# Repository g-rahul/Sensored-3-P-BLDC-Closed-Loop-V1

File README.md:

# Sensored-3-P-BLDC-Closed-Loop-V1
This Firmware was developed as an extension of  Ti's Sensored close-loop BLDC motor control using MSP430. 
Ti's application firmware for MSP430 has been modified for STM32F103 Series MCU's.

This firmware was developed by
* Rahul (rep owner)
* https://github.com/g-rahul
* RVCE
* July 2020

Target-STM32F103C8T6
IDE- MDK Keil uVision 5

The author would like to credit the orignal code developer on whose idea this code is based upon
 * Bhargavi Nisarga 
 * Texas Instruments Inc. 
 * Dec 2010
 * Built with IAR Version:4.2 and CCS v4.2
 
 More information on Ti's MSP430 application can be found at https://www.ti.com/lit/an/slaa503/slaa503.pdf?ts=1596031062777&ref_url=https%253A%252F%252Fwww.google.com%252F & 
 http://www.ti.com/lit/zip/slaa503.

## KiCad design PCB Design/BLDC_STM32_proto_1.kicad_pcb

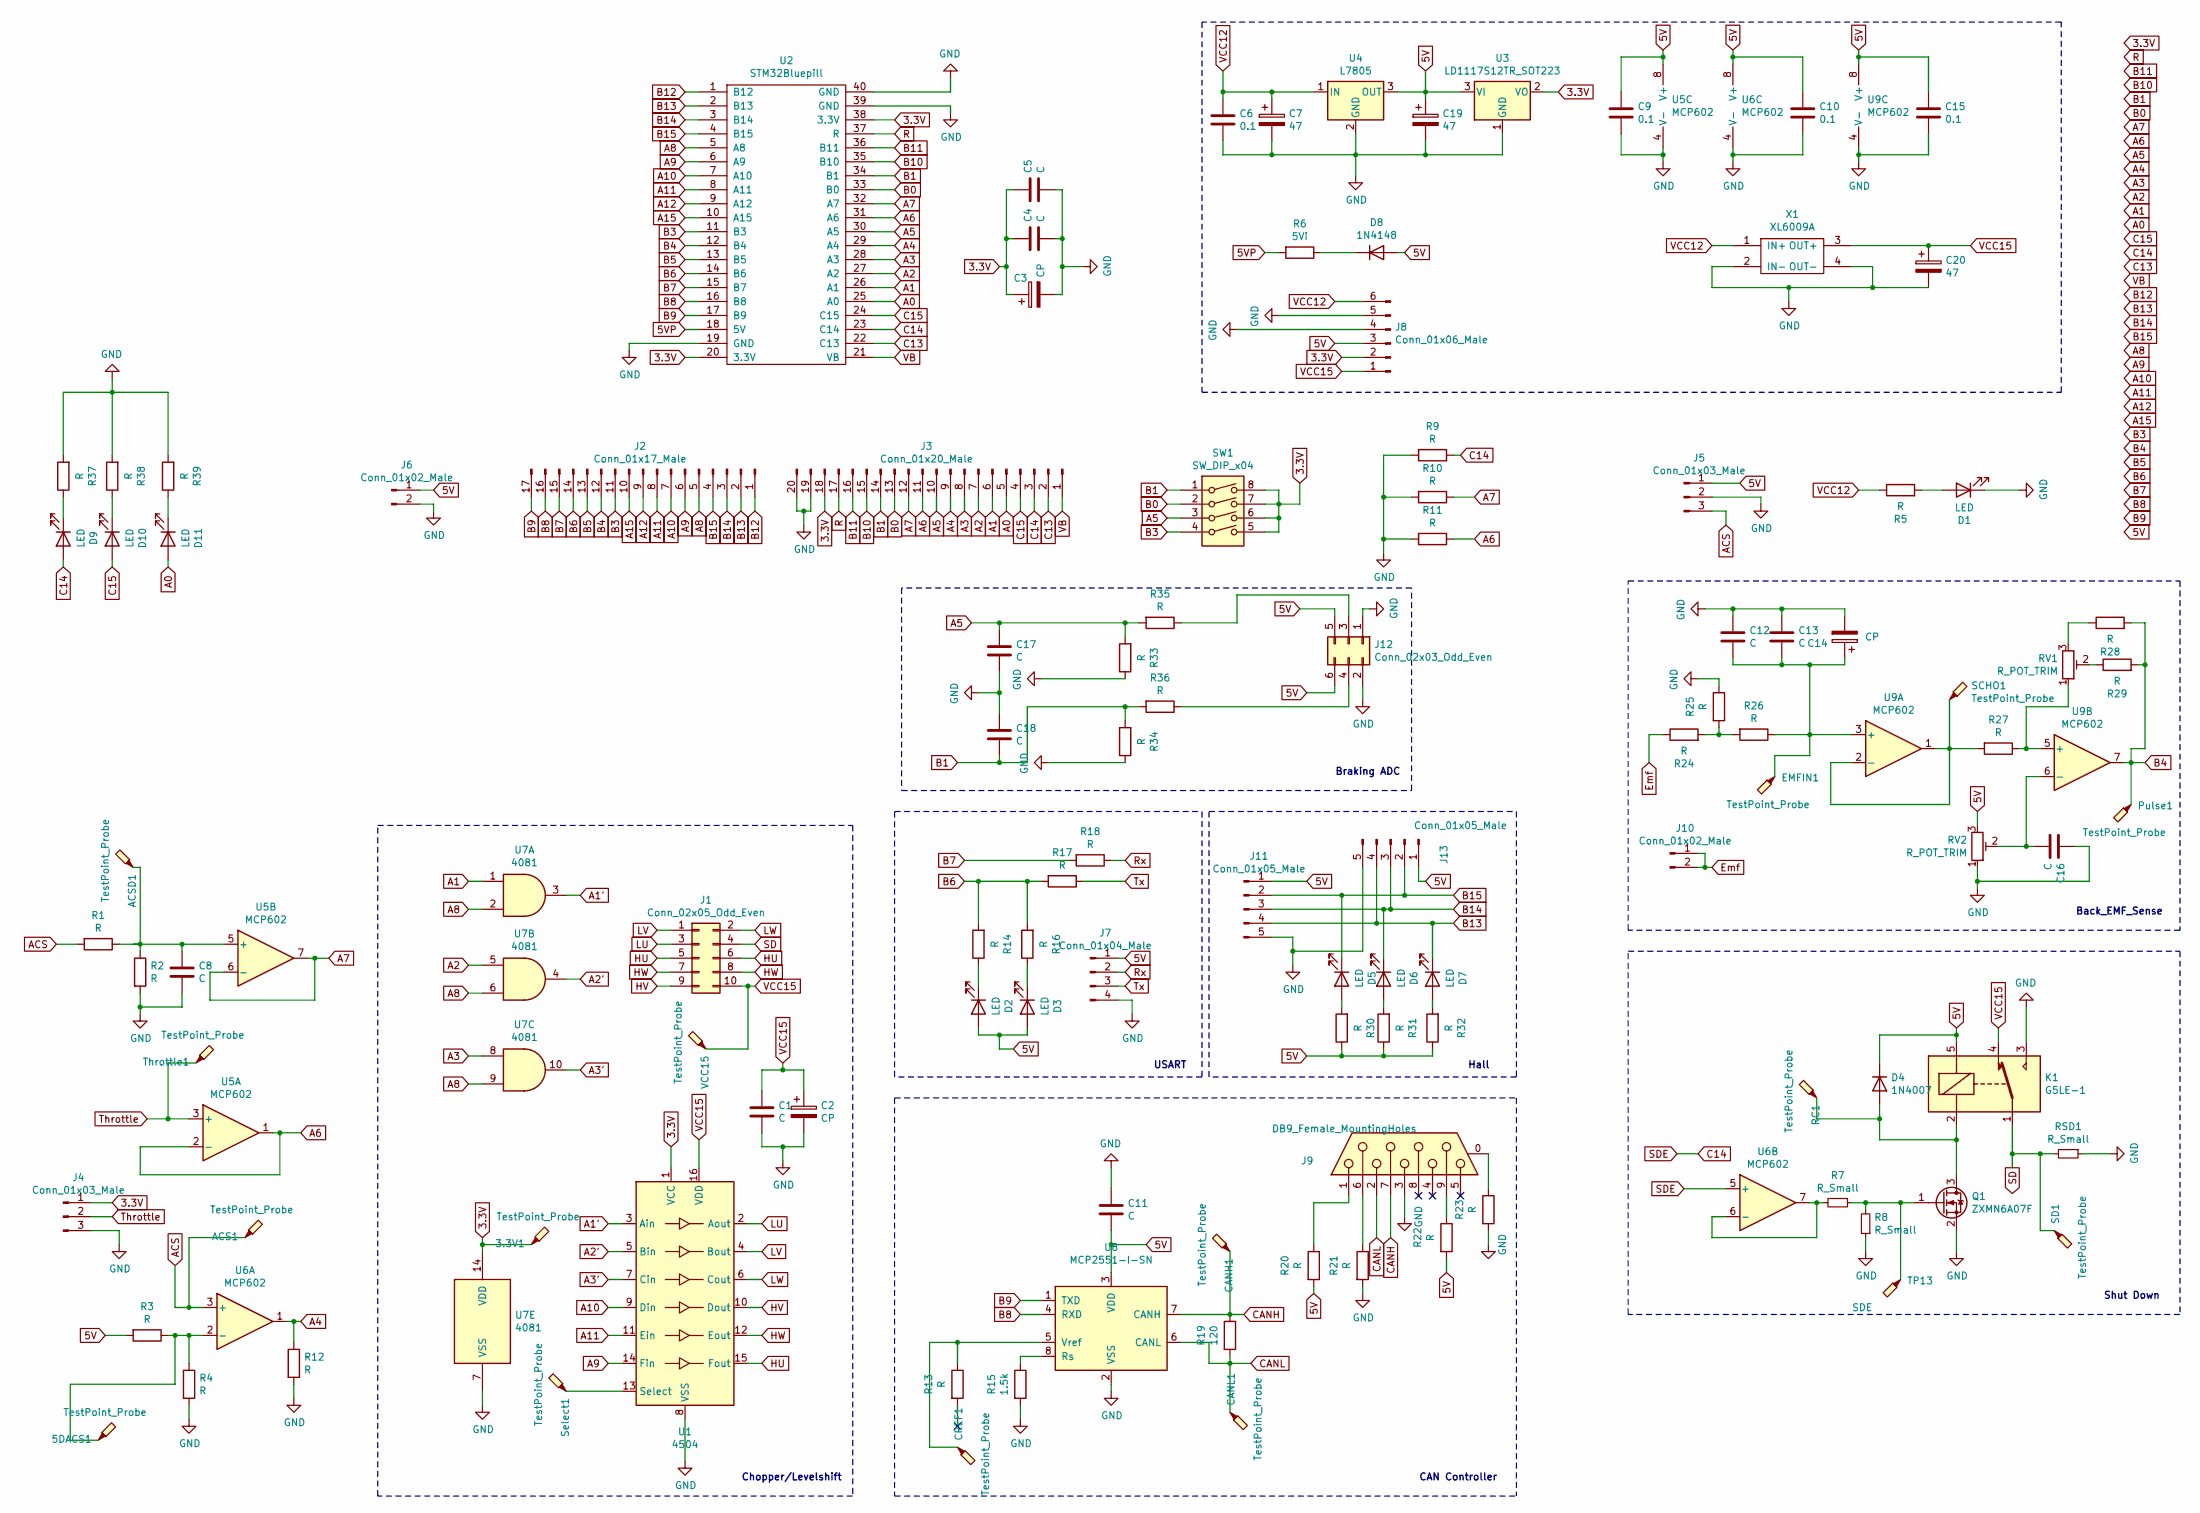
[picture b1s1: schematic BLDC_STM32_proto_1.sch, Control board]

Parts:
3.3V1, 5DACS1: TestPoint_Probe; TestPoint_Loop_D1.80mm_Drill1.0mm_Beaded
ACS1: TestPoint_Probe; TestPoint_Loop_D1.80mm_Drill1.0mm_Beaded
ACSD1: TestPoint_Probe; TestPoint_Loop_D1.80mm_Drill1.0mm_Beaded
C1, C4, C5, C8, C11, C12, C13, C16, C17, C18: C; C_1206_3216Metric_Pad1.42x1.75mm_HandSolder
C2, C3, C14: CP; CP_Radial_D8.0mm_P3.80mm
C6, C9, C10, C15: 0.1; C_1206_3216Metric_Pad1.42x1.75mm_HandSolder
C7, C19, C20: 47; CP_Radial_D8.0mm_P3.80mm
CANH1: TestPoint_Probe; TestPoint_Loop_D1.80mm_Drill1.0mm_Beaded
CANL1: TestPoint_Probe; TestPoint_Loop_D1.80mm_Drill1.0mm_Beaded
CREF1: TestPoint_Probe; TestPoint_Loop_D1.80mm_Drill1.0mm_Beaded
D1, D2, D3, D9, D10, D11: LED; LED_1206_3216Metric
D4: 1N4007; D_DO-41_SOD81_P10.16mm_Horizontal
D5, D6, D7: LED; LED_0805_2012Metric
D8: 1N4148; D_DO-35_SOD27_P7.62mm_Horizontal
EMFIN1: TestPoint_Probe; TestPoint_Loop_D1.80mm_Drill1.0mm_Beaded
J1: Conn_02x05_Odd_Even; IDC-Header_2x05_P2.54mm_Horizontal
J2: Conn_01x17_Male; PinSocket_1x17_P2.54mm_Vertical
J3: Conn_01x20_Male; PinSocket_1x20_P2.54mm_Vertical
J4, J5: Conn_01x03_Male; PinHeader_1x03_P2.54mm_Vertical
J6: Conn_01x02_Male; PinHeader_1x02_P2.54mm_Vertical
J7: Conn_01x04_Male; PinHeader_1x04_P2.54mm_Vertical
J8: Conn_01x06_Male; JST_VH_B6P-VH-B_1x06_P3.96mm_Vertical
J9: DB9_Female_MountingHoles; DSUB-9_Female_Horizontal_P2.77x2.84mm_EdgePinOffset9.90mm_H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
J10: Conn_01x02_Male; JST_VH_B2P-VH-B_1x02_P3.96mm_Vertical
J11: Conn_01x05_Male; JST_EH_B5B-EH-A_1x05_P2.50mm_Vertical
J12: Conn_02x03_Odd_Even; PinHeader_2x03_P2.54mm_Vertical_SMD
J13: Conn_01x05_Male; PinHeader_1x05_P2.54mm_Vertical
K1: G5LE-1; Relay_SPDT_Omron-G5LE-1
Pulse1: TestPoint_Probe; TestPoint_Loop_D1.80mm_Drill1.0mm_Beaded
Q1: ZXMN6A07F; SOT-23
R1, R2: R; R_Axial_DIN0207_L6.3mm_D2.5mm_P5.08mm_Vertical
R3, R4, R5, R9, R10, R11, R12, R13, R24, R25, R26, R27, R28, R29, R33, R34, R35, R36: R; R_1206_3216Metric_Pad1.42x1.75mm_HandSolder
R6: 5Vi; R_1206_3216Metric_Pad1.42x1.75mm_HandSolder
R7, R8: R_Small; R_1206_3216Metric_Pad1.42x1.75mm_HandSolder
R14, R16, R17, R18, R20, R21, R22, R23, R30, R31, R32, R37, R38, R39: R; R_0805_2012Metric
R15: 1.5k; R_1206_3216Metric_Pad1.42x1.75mm_HandSolder
R19: 120; R_1206_3216Metric_Pad1.42x1.75mm_HandSolder
RC1: TestPoint_Probe; TestPoint_Loop_D1.80mm_Drill1.0mm_Beaded
RSD1: R_Small; R_1206_3216Metric_Pad1.42x1.75mm_HandSolder
RV1, RV2: R_POT_TRIM; Potentiometer_Bourns_3296W_Vertical
SCHO1: TestPoint_Probe; TestPoint_Loop_D1.80mm_Drill1.0mm_Beaded
SD1: TestPoint_Probe; TestPoint_Loop_D1.80mm_Drill1.0mm_Beaded
SW1: SW_DIP_x04; DIP-8_W7.62mm_LongPads
Select1: TestPoint_Probe; TestPoint_Loop_D1.80mm_Drill1.0mm_Beaded
TP13: SDE; TestPoint_Loop_D1.80mm_Drill1.0mm_Beaded
Throttle1: TestPoint_Probe; TestPoint_Loop_D1.80mm_Drill1.0mm_Beaded
U1: 4504; DIP-16_W7.62mm
U2: STM32Bluepill
U3: LD1117S12TR_SOT223; SOT-223-3_TabPin2
U4: L7805; TO-263-2
U5, U6, U9: MCP602; SOIC-8_3.9x4.9mm_P1.27mm
U7: 4081; DIP-14_W7.62mm
U8: MCP2551-I-SN; SOIC-8_3.9x4.9mm_P1.27mm
VCC15: TestPoint_Probe; TestPoint_Loop_D1.80mm_Drill1.0mm_Beaded
X1: XL6009A; XL6009

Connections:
3.3V: 3.3V1.1, C3.1, C4.1, C5.1, J3.18, J4.1, J8.2, SW1.5, SW1.6, SW1.7, SW1.8, U1.1 (VCC), U2.20 (3.3V), U2.38 (3.3V), U3.2 (VO), U7.14 (VDD)
5V: C9.1, C10.1, C11.2, C15.1, C19.1, D2.2 (A), D3.2 (A), D4.1 (K), D8.2 (A), J5.1, J6.1, J7.1, J8.3, J11.1, J12.5, J12.6, J13.1, K1.5, R3.2, R20.2, R22.2, R30.1, R31.1, R32.1, RV2.3, U3.3 (VI), U4.3 (OUT), U5.8 (V+), U6.8 (V+), U8.3 (VDD), U9.8 (V+)
5VP: R6.2, U2.18 (5V)
A0: D11.2 (A), J3.5, U2.25 (A0)
A1: J3.6, U2.26 (A1), U7.1
A1': U1.3 (Ain), U7.3
A2: J3.7, U2.27 (A2), U7.5
A2': U1.5 (Bin), U7.4
A3: J3.8, U2.28 (A3), U7.8
A3': U1.7 (Cin), U7.10
A4: J3.9, R12.1, U2.29 (A4), U6.1
A5: C17.1, J3.10, R33.2, R35.2, SW1.3, U2.30 (A5)
A6: J3.11, R11.1, U2.31 (A6), U5.1, U5.2 (-)
A7: J3.12, R10.1, U2.32 (A7), U5.6 (-), U5.7
A8: J2.5, U2.5 (A8), U7.2, U7.6, U7.9
A9: J2.6, U1.14 (Fin), U2.6 (A9)
A10: J2.7, U1.9 (Din), U2.7 (A10)
A11: J2.8, U1.11 (Ein), U2.8 (A11)
A12: J2.9, U2.9 (A12)
A15: J2.10, U2.10 (A15)
ACS: ACS1.1, J5.3, R1.2, U6.3 (+)
B0: J3.13, SW1.2, U2.33 (B0)
B1: C18.2, J3.14, R34.2, R36.2, SW1.1, U2.34 (B1)
B3: J2.11, SW1.4, U2.11 (B3)
B4: J2.12, Pulse1.1, R28.2, R29.2, U2.12 (B4), U9.7
B5: J2.13, U2.13 (B5)
B6: J2.14, R14.2, R16.2, R17.2, U2.14 (B6)
B7: J2.15, R18.2, U2.15 (B7)
B8: J2.16, U2.16 (B8), U8.4 (RXD)
B9: J2.17, U2.17 (B9), U8.1 (TXD)
B10: J3.15, U2.35 (B10)
B11: J3.16, U2.36 (B11)
B12: J2.1, U2.1 (B12)
B13: D7.1 (K), J2.2, J11.4, J13.4, U2.2 (B13)
B14: D6.1 (K), J2.3, J11.3, J13.3, U2.3 (B14)
B15: D5.1 (K), J2.4, J11.2, J13.2, U2.4 (B15)
C13: J3.2, U2.22 (C13)
C14: D9.2 (A), J3.3, R9.1, U2.23 (C14), U6.5 (+)
C15: D10.2 (A), J3.4, U2.24 (C15)
CANH: CANH1.1, J9.7, R19.1, U8.7 (CANH)
CANL: CANL1.1, J9.2, R19.2, U8.6 (CANL)
Emf: J10.1, J10.2, R24.1
GND: C1.2, C2.2, C3.2, C4.2, C5.2, C6.2, C7.2, C8.2, C9.2, C10.2, C11.1, C12.1, C13.1, C14.2, C15.2, C16.1, C17.2, C18.1, C19.2, C20.2, D1.1 (K), J3.19, J3.20, J4.3, J5.2, J6.2, J7.4, J8.4, J8.5, J9.3, J11.5, J12.1, J12.2, J13.5, K1.3, Q1.2 (S), R2.2, R4.2, R8.1, R9.2, R10.2, R11.2, R12.2, R15.2, R21.2, R23.2, R25.1, R33.1, R34.1, R37.2, R38.2, R39.2, RSD1.1, RV2.1, U1.8 (VSS), U2.19 (GND), U2.39 (GND), U2.40 (GND), U3.1 (GND), U4.2 (GND), U5.4 (V-), U6.4 (V-), U7.7 (VSS), U8.2 (VSS), U9.4 (V-), X1.2 (IN-), X1.4 (OUT-); also elsewhere on the board
HU: J1.5, J1.6, U1.15 (Fout)
HV: J1.9, U1.10 (Dout)
HW: J1.7, J1.8, U1.12 (Eout)
LU: J1.3, U1.2 (Aout)
LV: J1.1, U1.4 (Bout)
LW: J1.2, U1.6 (Cout)
unnamed: 5DACS1.1, R3.1, R4.1, U6.2 (-)
unnamed: ACSD1.1, C8.1, R1.1, R2.1, U5.5 (+)
unnamed: C12.2, C13.2, C14.1, EMFIN1.1, R26.1, U9.3 (+)
unnamed: C16.2, RV2.2, U9.6 (-)
unnamed: CREF1.1, R13.1, U8.5 (Vref)
unnamed: D1.2 (A), R5.2
unnamed: D2.1 (K), R14.1
unnamed: D3.1 (K), R16.1
unnamed: D4.2 (A), K1.2, Q1.3 (D), RC1.1
unnamed: D5.2 (A), R30.2
unnamed: D6.2 (A), R31.2
unnamed: D7.2 (A), R32.2
unnamed: D8.1 (K), R6.1
unnamed: D9.1 (K), R37.1
unnamed: D10.1 (K), R38.1
unnamed: D11.1 (K), R39.1
unnamed 65: J9.0 (PAD), R23.1; also elsewhere on the board
unnamed: J9.1, R20.1
unnamed: J9.6, R21.1
unnamed: J9.9, R22.1
unnamed: J12.3, R35.1
unnamed: J12.4, R36.1
unnamed: Q1.1 (G), R7.1, R8.2, TP13.1
unnamed: R7.2, U6.6 (-), U6.7
unnamed: R15.1, U8.8 (Rs)
unnamed: R24.2, R25.2, R26.2
unnamed: R27.1, RV1.1, U9.5 (+)
unnamed: R27.2, SCHO1.1, U9.1, U9.2 (-)
unnamed: R28.1, RV1.3
unnamed: R29.1, RV1.2
unnamed: Select1.1, U1.13 (Select)
R: J3.17, U2.37 (R)
Rx: J7.2, R18.1
SD: J1.4, K1.1, RSD1.2, SD1.1
Throttle: J4.2, Throttle1.1, U5.3 (+)
Tx: J7.3, R17.1
VB: J3.1, U2.21 (VB)
VCC12: C6.1, C7.1, J8.6, R5.1, U4.1 (IN), X1.1 (IN+)
VCC15: C1.1, C2.1, C20.1, J1.10, J8.1, K1.4, U1.16 (VDD), VCC15.1, X1.3 (OUT+)

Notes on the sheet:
CAN Controller
Shut Down
USART
Back_EMF_Sense
Chopper/Levelshift
Hall
Braking ADC

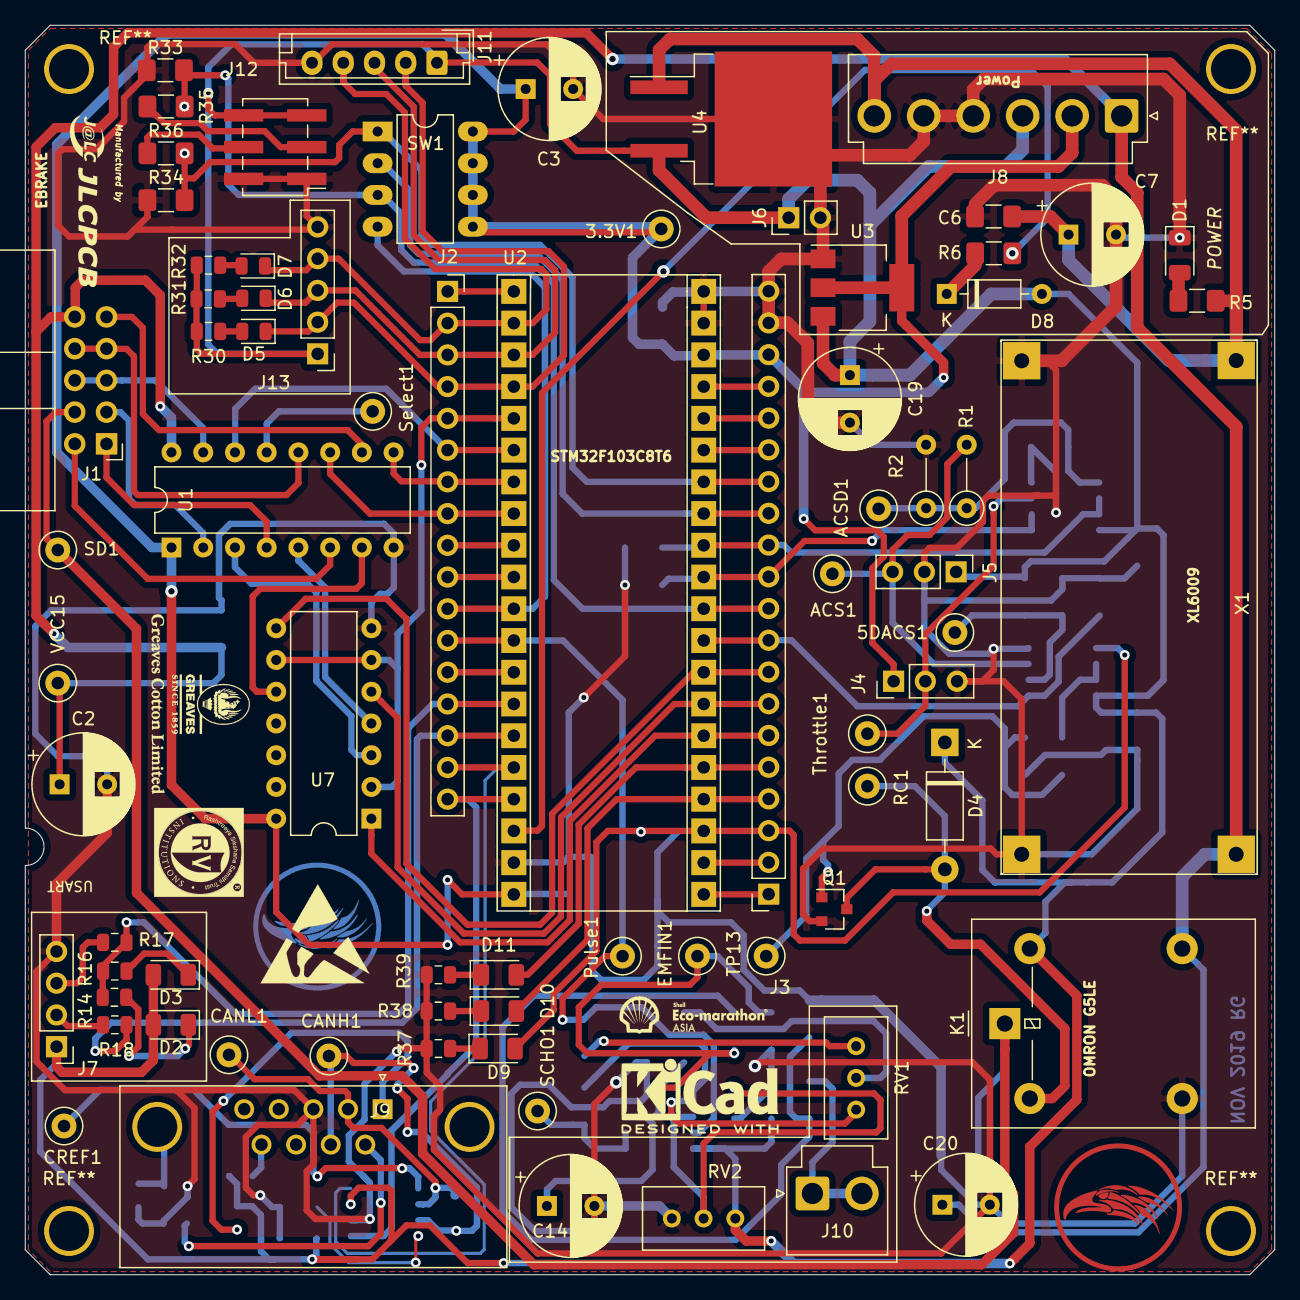
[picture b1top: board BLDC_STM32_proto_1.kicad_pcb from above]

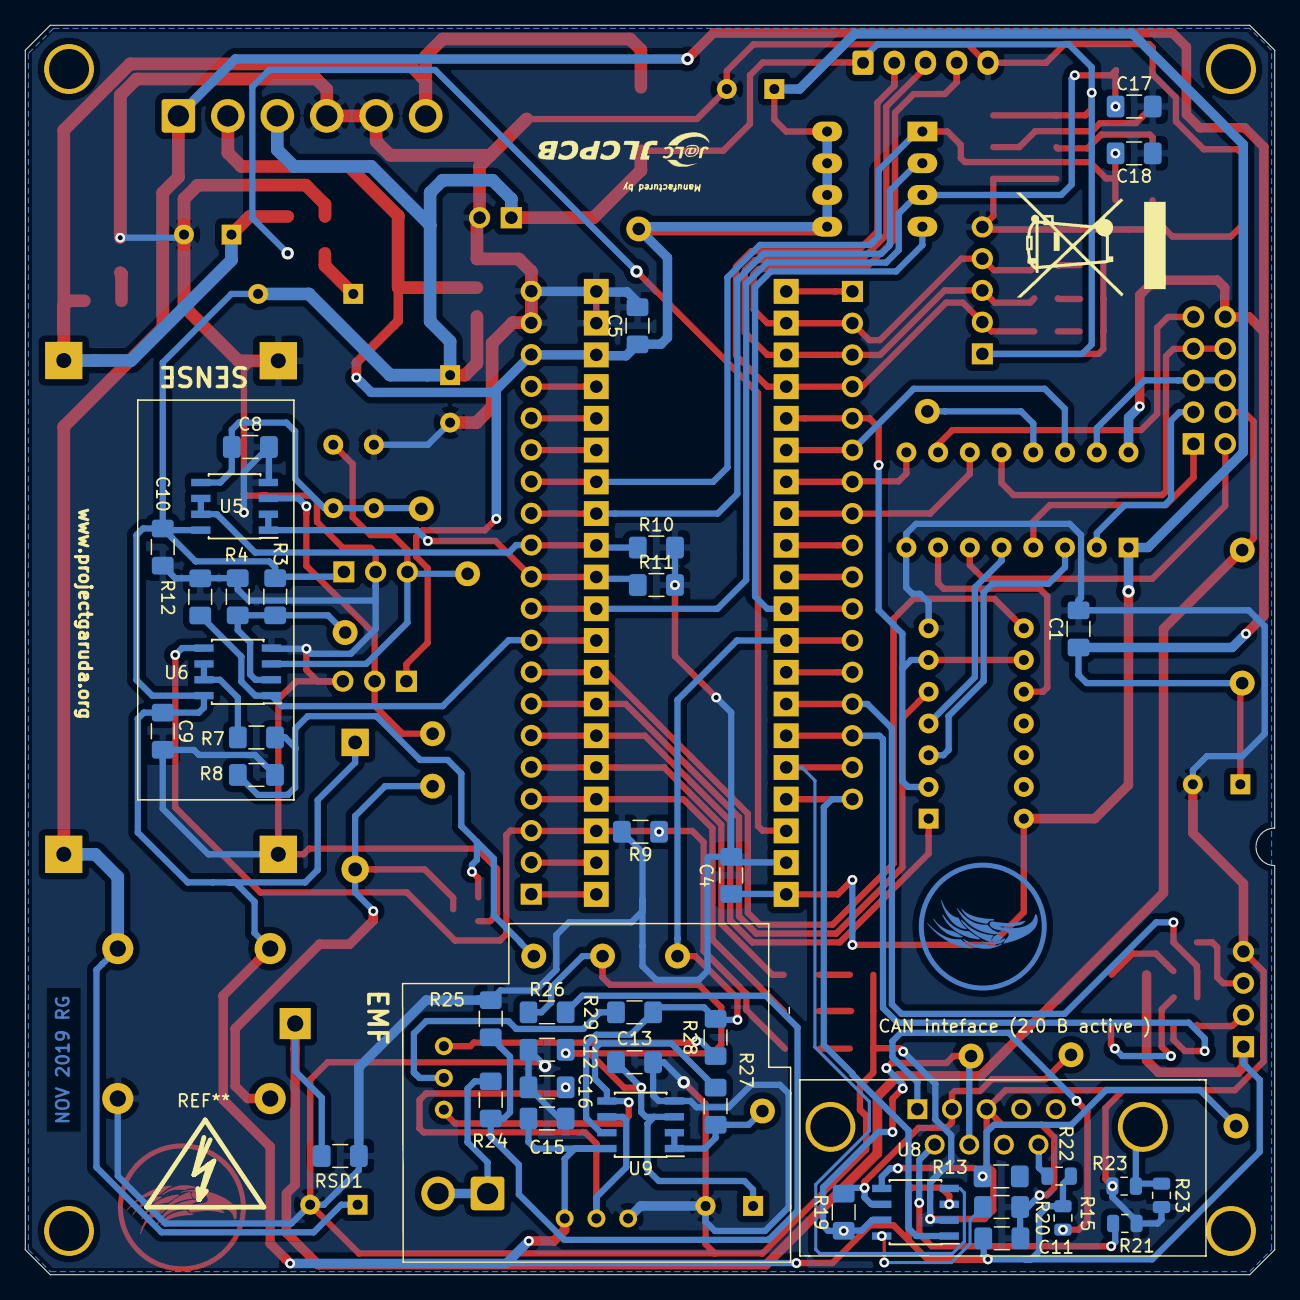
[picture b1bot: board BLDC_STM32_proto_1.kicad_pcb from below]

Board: 2 copper layers, 100.0 x 100.0 mm, 116 parts (40 on the bottom side), 88 nets.

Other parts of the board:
R23#2: R; R_0805_2012Metric

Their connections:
GND: R23#2.2; also elsewhere on the board
unnamed 65: R23#2.1; also elsewhere on the board

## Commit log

2020-07-29 second random
2020-07-31 added pcb design files
2020-08-01 1/8/2020 commit - lot of new features added check MC_Readme
2020-08-25 modifications
2020-08-26 added trip and enable
